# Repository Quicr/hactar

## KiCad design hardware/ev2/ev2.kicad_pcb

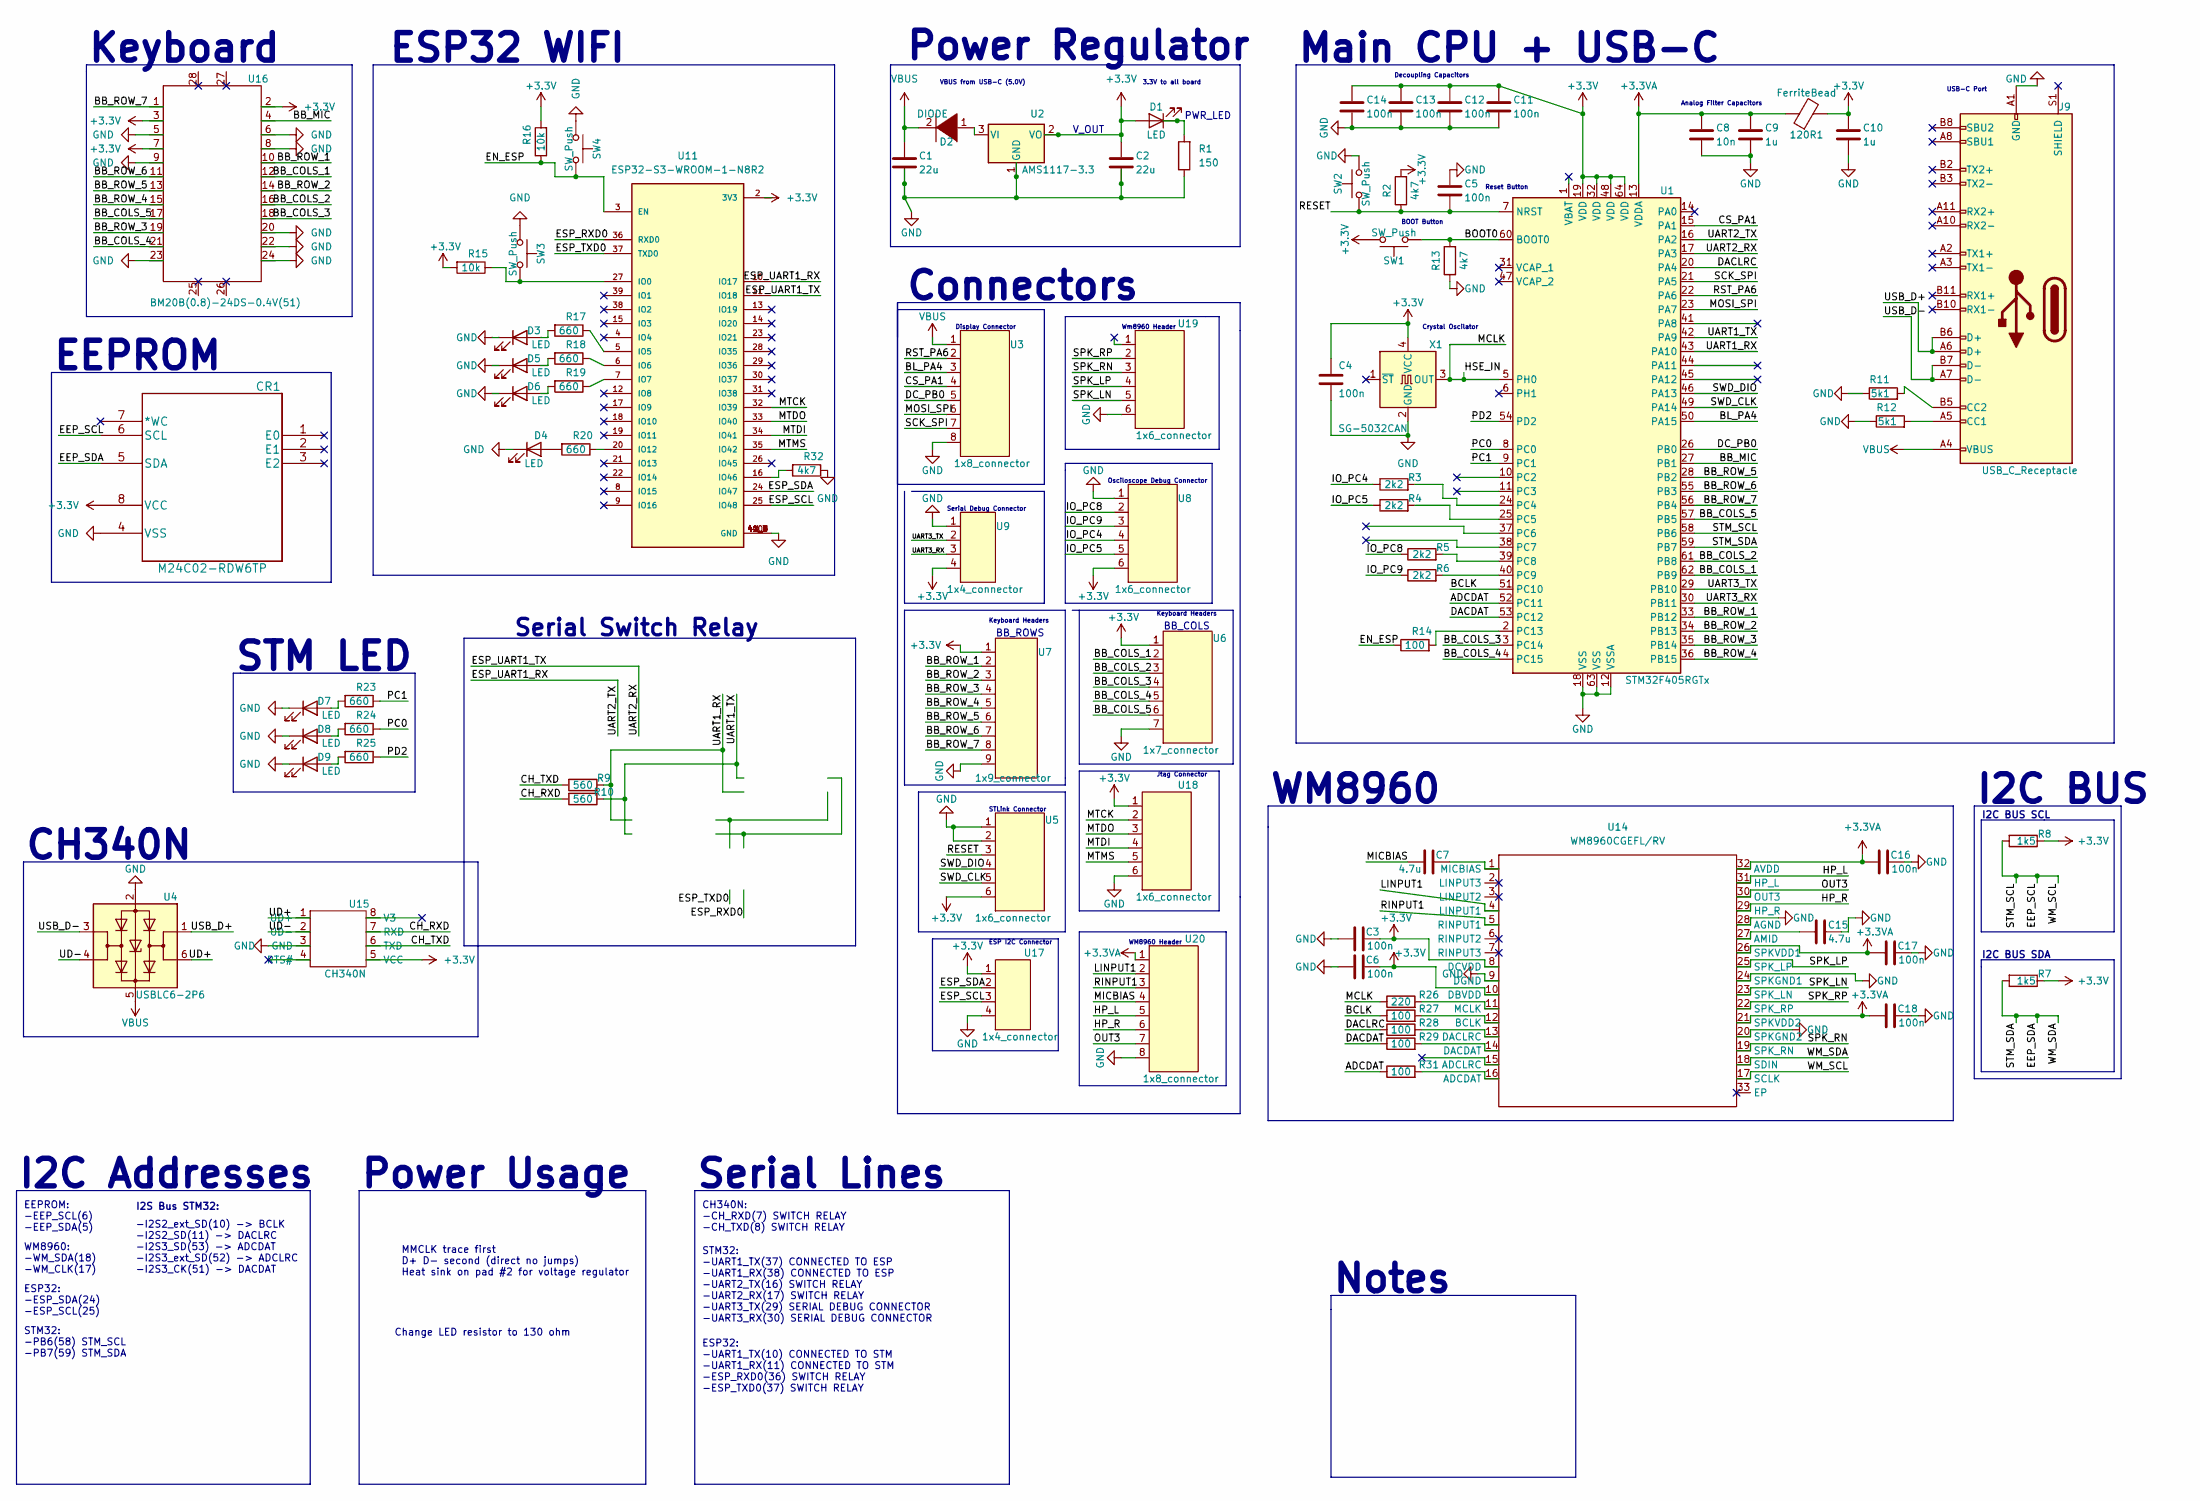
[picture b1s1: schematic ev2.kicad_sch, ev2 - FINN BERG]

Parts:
120R1: FerriteBead; L_0805_2012Metric
C1, C2: 22u; C_0805_2012Metric
C3, C4, C5, C6, C11, C12, C13, C14, C16, C17, C18: 100n; C_0805_2012Metric
C7, C15: 4.7u; C_0805_2012Metric
C8: 10n; C_0805_2012Metric
C9, C10: 1u; C_0805_2012Metric
CR1: M24C02-RDW6TP; New_ESP32_M24C02-RMN6TP
D1, D3, D4, D5, D6, D7, D8, D9: LED; LED_0805_2012Metric
D2: DIODE; D_0805_2012Metric
J9: USB_C_Receptacle; USB_C_Receptacle_HRO_TYPE-C-31-M-12
R1: 150; R_0805_2012Metric
R2, R13, R32: 4k7; R_0805_2012Metric
R3, R4, R5, R6: 2k2; R_0805_2012Metric
R7, R8: 1k5; R_0805_2012Metric
R9, R10: 560; R_0805_2012Metric
R11, R12: 5k1; R_0805_2012Metric
R14, R27, R28, R29, R31: 100; R_0805_2012Metric
R15, R16: 10k; R_0805_2012Metric
R17, R18, R19, R20, R23, R24, R25: 660; R_0805_2012Metric
R26: 220; R_0805_2012Metric
SW1, SW2, SW3, SW4: SW_Push; SW_DIP_SPSTx01_Slide_6.7x4.1mm_W6.73mm_P2.54mm_LowProfile_J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
U1: STM32F405RGTx; LQFP-64_10x10mm_P0.5mm
U2: AMS1117-3.3; SOT-223-3_TabPin2
U3, U20: 1x8_connector; 1X8_CONNECTOR
U4: USBLC6-2P6; SOT-666
U5, U8, U18, U19: 1x6_connector
U6: 1x7_connector
U7: 1x9_connector
U9, U17: 1x4_connector
U11: ESP32-S3-WROOM-1-N8R2
U14: WM8960CGEFL/RV; QFN50P500X500X90-33N
U15: CH340N; SOIC127P600X180-16N
U16: BM20B(0.8)-24DS-0.4V(51)
X1: SG-5032CAN; Oscillator_SMD_SeikoEpson_SG8002LB-4Pin_5.0x3.2mm

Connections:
+3.3V: 120R1.2, C2.1, C3.2, C4.1, C6.2, C10.1, C11.1, C12.1, C13.1, C14.1, CR1.8 (VCC), D1.2 (A), R2.2, R7.1, R8.1, R15.2, R16.2, SW1.1, U1.19 (VDD), U1.32 (VDD), U1.48 (VDD), U1.64 (VDD), U2.2 (VO), U5.6, U6.1, U7.1, U8.6, U9.4, U11.2 (3V3), U14.8 (DCVDD), U14.10 (DBVDD), U15.5 (VCC), U16.2, U16.3, U16.7, U17.1, U18.1, X1.4 (VCC)
+3.3VA: 120R1.1, C8.1, C9.1, C16.1, C17.1, C18.1, U1.13 (VDDA), U14.21 (SPKVDD2), U14.26 (SPKVDD1), U14.32 (AVDD), U20.1
/ADCDAT: R31.1, U1.52 (PC11)
/BB_COLS_1: U1.62 (PB9), U6.2, U16.12
/BB_COLS_2: U1.61 (PB8), U6.3, U16.16
/BB_COLS_3: U1.3 (PC14), U6.4, U16.18
/BB_COLS_4: U1.4 (PC15), U6.5, U16.21
/BB_COLS_5: U1.57 (PB5), U6.6, U16.17
/BB_MIC: U1.27 (PB1), U16.4
/BB_ROW_1: U1.33 (PB12), U7.2, U16.10
/BB_ROW_2: U1.34 (PB13), U7.3, U16.14
/BB_ROW_3: U1.35 (PB14), U7.4, U16.19
/BB_ROW_4: U1.36 (PB15), U7.5, U16.15
/BB_ROW_5: U1.28 (PB2), U7.6, U16.13
/BB_ROW_6: U1.55 (PB3), U7.7, U16.11
/BB_ROW_7: U1.56 (PB4), U7.8, U16.1
/BCLK: R27.1, U1.51 (PC10)
/BL_PA4: U1.50 (PA15), U3.3
/BOOT0: R13.2, SW1.2, U1.60 (BOOT0)
/CH_RXD: R10.2, U15.7 (RXD)
/CH_TXD: R9.2, U15.6 (TXD)
/CS_PA1: U1.15 (PA1), U3.4
/DACDAT: R29.1, U1.53 (PC12)
/DACLRC: R28.1, U1.20 (PA4)
/DC_PB0: U1.26 (PB0), U3.5
/EEP_SCL: CR1.6 (SCL), R8.2, U1.58 (PB6), U14.17 (SCLK)
/EEP_SDA: CR1.5 (SDA), R7.2, U1.59 (PB7), U14.18 (SDIN)
/EN_ESP: R14.1, R16.1, SW4.1, U11.3 (EN)
/ESP_RXD0: U11.36 (RXD0)
/ESP_SCL: U11.25 (IO48), U17.3
/ESP_SDA: U11.24 (IO47), U17.2
/ESP_TXD0: U11.37 (TXD0)
/ESP_UART1_RX: U1.16 (PA2), U11.10 (IO17)
/ESP_UART1_TX: U1.17 (PA3), U11.11 (IO18)
/HP_L: U14.31 (HP_L), U20.5
/HP_R: U14.29 (HP_R), U20.6
/HSE_IN: R26.1, U1.5 (PH0), X1.3 (OUT)
/IO_PC4: R3.1, U8.4
/IO_PC5: R4.1, U8.5
/IO_PC8: R5.1, U8.2
/IO_PC9: R6.1, U8.3
/LINPUT1: U14.4 (LINPUT1), U20.2
/MICBIAS: C7.1, U20.4
/MOSI_SPI: U1.23 (PA7), U3.6
/MTCK: U11.32 (IO39), U18.2
/MTDI: U11.34 (IO41), U18.4
/MTDO: U11.33 (IO40), U18.3
/MTMS: U11.35 (IO42), U18.5
/OUT3: U14.30 (OUT3), U20.7
/PC0: R24.1, U1.8 (PC0)
/PC1: R23.1, U1.9 (PC1)
/PD2: R25.1, U1.54 (PD2)
/RESET: C5.2, R2.1, SW2.2, U1.7 (NRST), U5.3
/RINPUT1: U14.5 (RINPUT1), U20.3
/RST_PA6: U1.22 (PA6), U3.2
/SCK_SPI: U1.21 (PA5), U3.7
/SPK_LN: U14.23 (SPK_LN), U19.5
/SPK_LP: U14.25 (SPK_LP), U19.4
/SPK_RN: U14.19 (SPK_RN), U19.3
/SPK_RP: U14.22 (SPK_RP), U19.2
/SWD_CLK: U1.49 (PA14), U5.5
/SWD_DIO: U1.46 (PA13), U5.4
/UART1_RX: R9.1, U1.43 (PA10)
/UART1_TX: R10.1, U1.42 (PA9)
/UART3_RX: U1.30 (PB11), U9.3
/UART3_TX: U1.29 (PB10), U9.2
/UD+: U4.6 (I/O1), U15.1 (UD+)
/UD-: U4.4 (I/O2), U15.2 (UD-)
/USB_D+: J9.A6 (D+), J9.B6 (D+), U4.1 (I/O1)
/USB_D-: J9.A7 (D-), J9.B7 (D-), U4.3 (I/O2)
GND: C1.2, C2.2, C3.1, C4.2, C5.1, C6.1, C8.2, C9.2, C10.2, C11.2, C12.2, C13.2, C14.2, C15.1, C16.2, C17.2, C18.2, CR1.4 (VSS), D3.1 (K), D4.1 (K), D5.1 (K), D6.1 (K), D7.1 (K), D8.1 (K), D9.1 (K), J9.A1 (GND), J9.A12 (GND), J9.B1 (GND), J9.B12 (GND), R1.1, R11.1, R12.1, R13.1, R32.1, SW2.1, SW3.2, SW4.2, U1.12 (VSSA), U1.18 (VSS), U1.63 (VSS), U2.1 (GND), U3.8, U4.2 (GND), U5.1, U5.2, U6.7, U7.9, U8.1, U9.1, U11.1 (GND), U11.40 (GND), U11.41_1 (GND), U11.41_2 (GND), U11.41_3 (GND), U11.41_4 (GND), U11.41_5 (GND), U11.41_6 (GND), U11.41_7 (GND), U11.41_8 (GND), U11.41_9 (GND), U14.9 (DGND), U14.20 (SPKGND2), U14.24 (SPKGND1), U14.28 (AGND), U15.3 (GND), U16.5, U16.6, U16.8, U16.9, U16.20, U16.22, U16.23, U16.24, U17.4, U18.6, U19.6, U20.8, X1.2 (GND)
unnamed: C7.2, U14.1 (MICBIAS)
unnamed: C15.2, U14.27 (AMID)
unnamed: D1.1 (K), R1.2
unnamed: D2.1 (K), U2.3 (VI)
unnamed: D3.2 (A), R17.2
unnamed: D4.2 (A), R20.2
unnamed: D5.2 (A), R18.2
unnamed: D6.2 (A), R19.2
unnamed: D7.2 (A), R23.2
unnamed: D8.2 (A), R24.2
unnamed: D9.2 (A), R25.2
unnamed: J9.A5 (CC1), R12.2
unnamed: J9.B5 (CC2), R11.2
unnamed: R3.2, U1.24 (PC4)
unnamed: R4.2, U1.25 (PC5)
unnamed: R5.2, U1.39 (PC8)
unnamed: R6.2, U1.40 (PC9)
unnamed: R14.2, U1.2 (PC13)
unnamed: R15.1, SW3.1, U11.27 (IO0)
unnamed: R17.1, U11.5 (IO5)
unnamed: R18.1, U11.6 (IO6)
unnamed: R19.1, U11.7 (IO7)
unnamed: R20.1, U11.20 (IO12)
unnamed: R26.2, U14.11 (MCLK)
unnamed: R27.2, U14.12 (BCLK)
unnamed: R28.2, U14.13 (DACLRC)
unnamed: R29.2, U14.14 (DACDAT)
unnamed: R31.2, U14.16 (ADCDAT)
unnamed: R32.2, U11.16 (IO46)
VBUS: C1.1, D2.2 (A), J9.A4 (VBUS), J9.A9 (VBUS), J9.B4 (VBUS), J9.B9 (VBUS), U3.1, U4.5 (VBUS)

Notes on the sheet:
STM32: -UART1_TX(37) CONNECTED TO ESP -UART1_RX(38) CONNECTED TO ESP -UART2_TX(16) SWITCH RELAY -UART2_RX(17) SWITCH RELAY -UART3_TX(29) SERIAL DEBUG CONNECTOR -UART3_RX(30) SERIAL DEBUG CONNECTOR
Serial Switch Relay
EEPROM: -EEP_SCL(6) -EEP_SDA(5)
I2S Bus STM32:
BB_COLS
ESP32: -ESP_SDA(24) -ESP_SCL(25)
ESP32 WIFI
Analog Filter Capacitors
I2C BUS SCL
PWR_LED
Keyboard Headers
Crystal Oscilator
CH340N: -CH_RXD(7) SWITCH RELAY -CH_TXD(8) SWITCH RELAY
3.3V to all board
BB_ROWS
Decoupling Capacitors
Main CPU + USB-C
Serial Debug Connector
-I2S2_ext_SD(10) -> BCLK -I2S2_SD(11) -> DACLRC -I2S3_SD(53) -> ADCDAT -I2S3_ext_SD(52) -> ADCLRC -I2S3_CK(51) -> DACDAT
ESP32: -UART1_TX(10) CONNECTED TO STM -UART1_RX(11) CONNECTED TO STM -ESP_RXD0(36) SWITCH RELAY -ESP_TXD0(37) SWITCH RELAY
Notes
MMCLK trace first D+ D- second (direct no jumps) Heat sink on pad #2 for voltage regulator
Power Usage
WM8960
I2C BUS SDA
V_OUT
STM32: -PB6(58) STM_SCL -PB7(59) STM_SDA
EEPROM
Display Connector
I2C BUS
WM8960: -WM_SDA(18) -WM_CLK(17)
I2C Addresses
VBUS from USB-C (5.0V)
Serial Lines
Power Regulator
Keyboard
Change LED resistor to 130 ohm
Connectors
WM8960 Header
STLink Connector

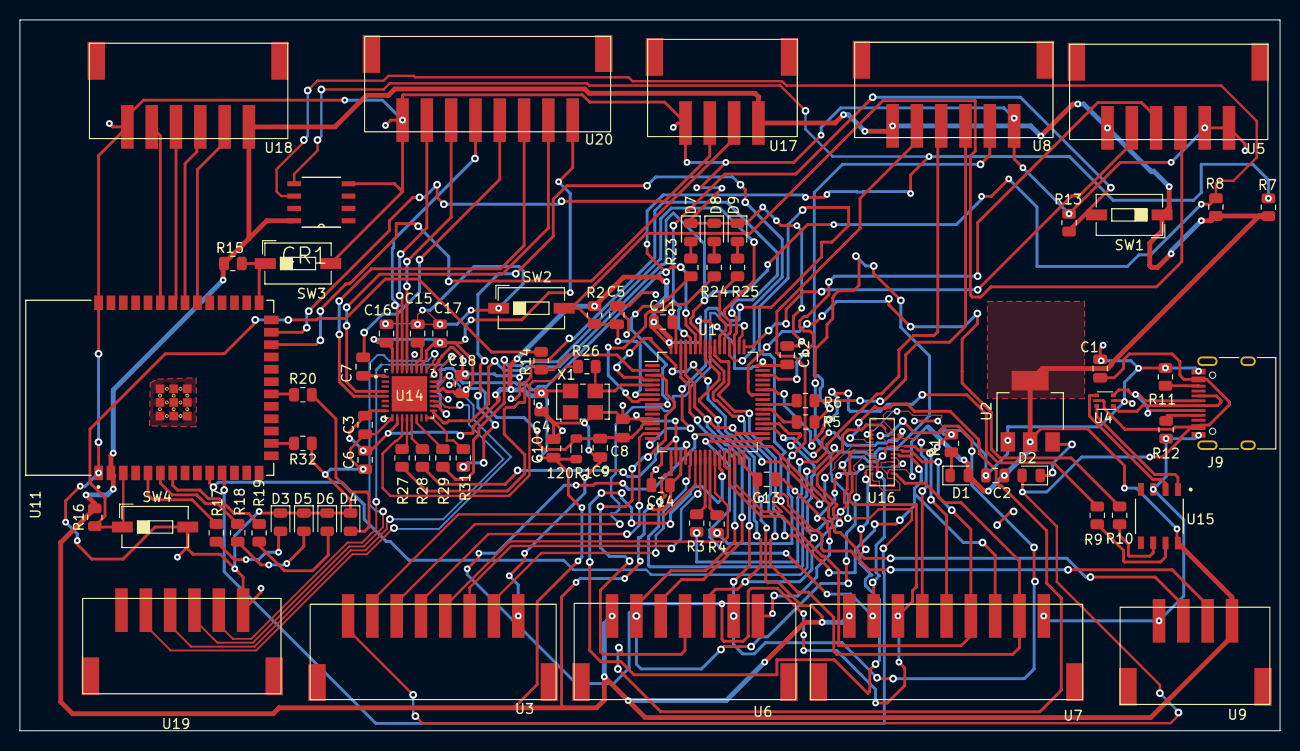
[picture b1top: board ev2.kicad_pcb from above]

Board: 2 copper layers, 129.6 x 73.1 mm, 81 parts (0 on the bottom side), 99 nets.

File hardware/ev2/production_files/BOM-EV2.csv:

Comment,Designator,Footprint,LCSC
FerriteBead,120R1,L_0805_2012Metric,C127301
LED,"D1,D3,D4,D5,D6,D7,D8,D9",LED_0805_2012Metric,C130114
DIODE,D2,D_0805_2012Metric,C133103
STM32F405RGTx,U1,LQFP-64_10x10mm_P0.5mm,C15742
USB_C_Receptacle,J9,USB_C_Receptacle_HRO_TYPE-C-31-M-12,C165948
10n,C8,C_0805_2012Metric,C1710
660,"R17,R18,R19,R20,R23,R24,R25",R_0805_2012Metric,C17455
150,R1,R_0805_2012Metric,C17471
2k2,"R3,R4,R5,R6",R_0805_2012Metric,C17520
4k7,"R13,R2,R32",R_0805_2012Metric,C17673
WM8960CGEFL/RV,U14,QFN50P500X500X90-33N,C18752
SG-5032CAN,X1,Oscillator_SMD_SeikoEpson_SG8002LB-4Pin_5.0x3.2mm,C1987261
100,"R14,R27,R28,R29,R31",R_0805_2012Metric,C212282
SW_Push,"SW1,SW2,SW3,SW4",SW_DIP_SPSTx01_Slide_6.7x4.1mm_W6.73mm_P2.54mm_LowProfile_JPin,C266189
5k1,"R11,R12",R_0805_2012Metric,C27834
USBLC6-2P6,U4,SOT-666,C2827693
1u,"C10,C9",C_0805_2012Metric,C28323
1x4_connector,"U17,U9",1x4_connector,C2845685
1x6_connector,"U18,U19,U5,U8",1x6_connector,C2845687
1x7_connector,U6,1x7_connector,C2845688
1x8_connector,"U20,U3",1X8_CONNECTOR,C2845689
1x9_connector,U7,1x9_connector,C2845690
ESP32-S3-WROOM-1-N8R2,U11,ESP32-S3-WROOM-1-N8R2,C2913204
SW_DIP_x02,"SW5,SW6,SW7,SW8",SW_DIP_SPSTx02_Slide_6.7x6.64mm_W6.73mm_P2.54mm_LowProfile_JPin,C3293152
AMS1117-3.3,U2,SOT-223-3_TabPin2,C351784
560,"R10,R21,R22,R9",R_0805_2012Metric,C374648
220,R26,R_0805_2012Metric,C374734
4.7u,"C15,C7",C_0805_2012Metric,C412634
BM20B(0.8)-24DS-0.4V(51),U16,BM20B(0.8)-24DS-0.4V(51),C424537
1k5,"R7,R8",R_0805_2012Metric,C4310
22u,"C1,C2",C_0805_2012Metric,C45783
10k,"R15,R16",R_0805_2012Metric,C465472
100n,"C11,C12,C13,C14,C16,C17,C18,C3,C4,C5,C6",C_0805_2012Metric,C49678
CH340N,U15,SOIC127P600X180-16N,C506813
M24C02-RDW6TP,CR1,M24C02-RDW6TP,C83836

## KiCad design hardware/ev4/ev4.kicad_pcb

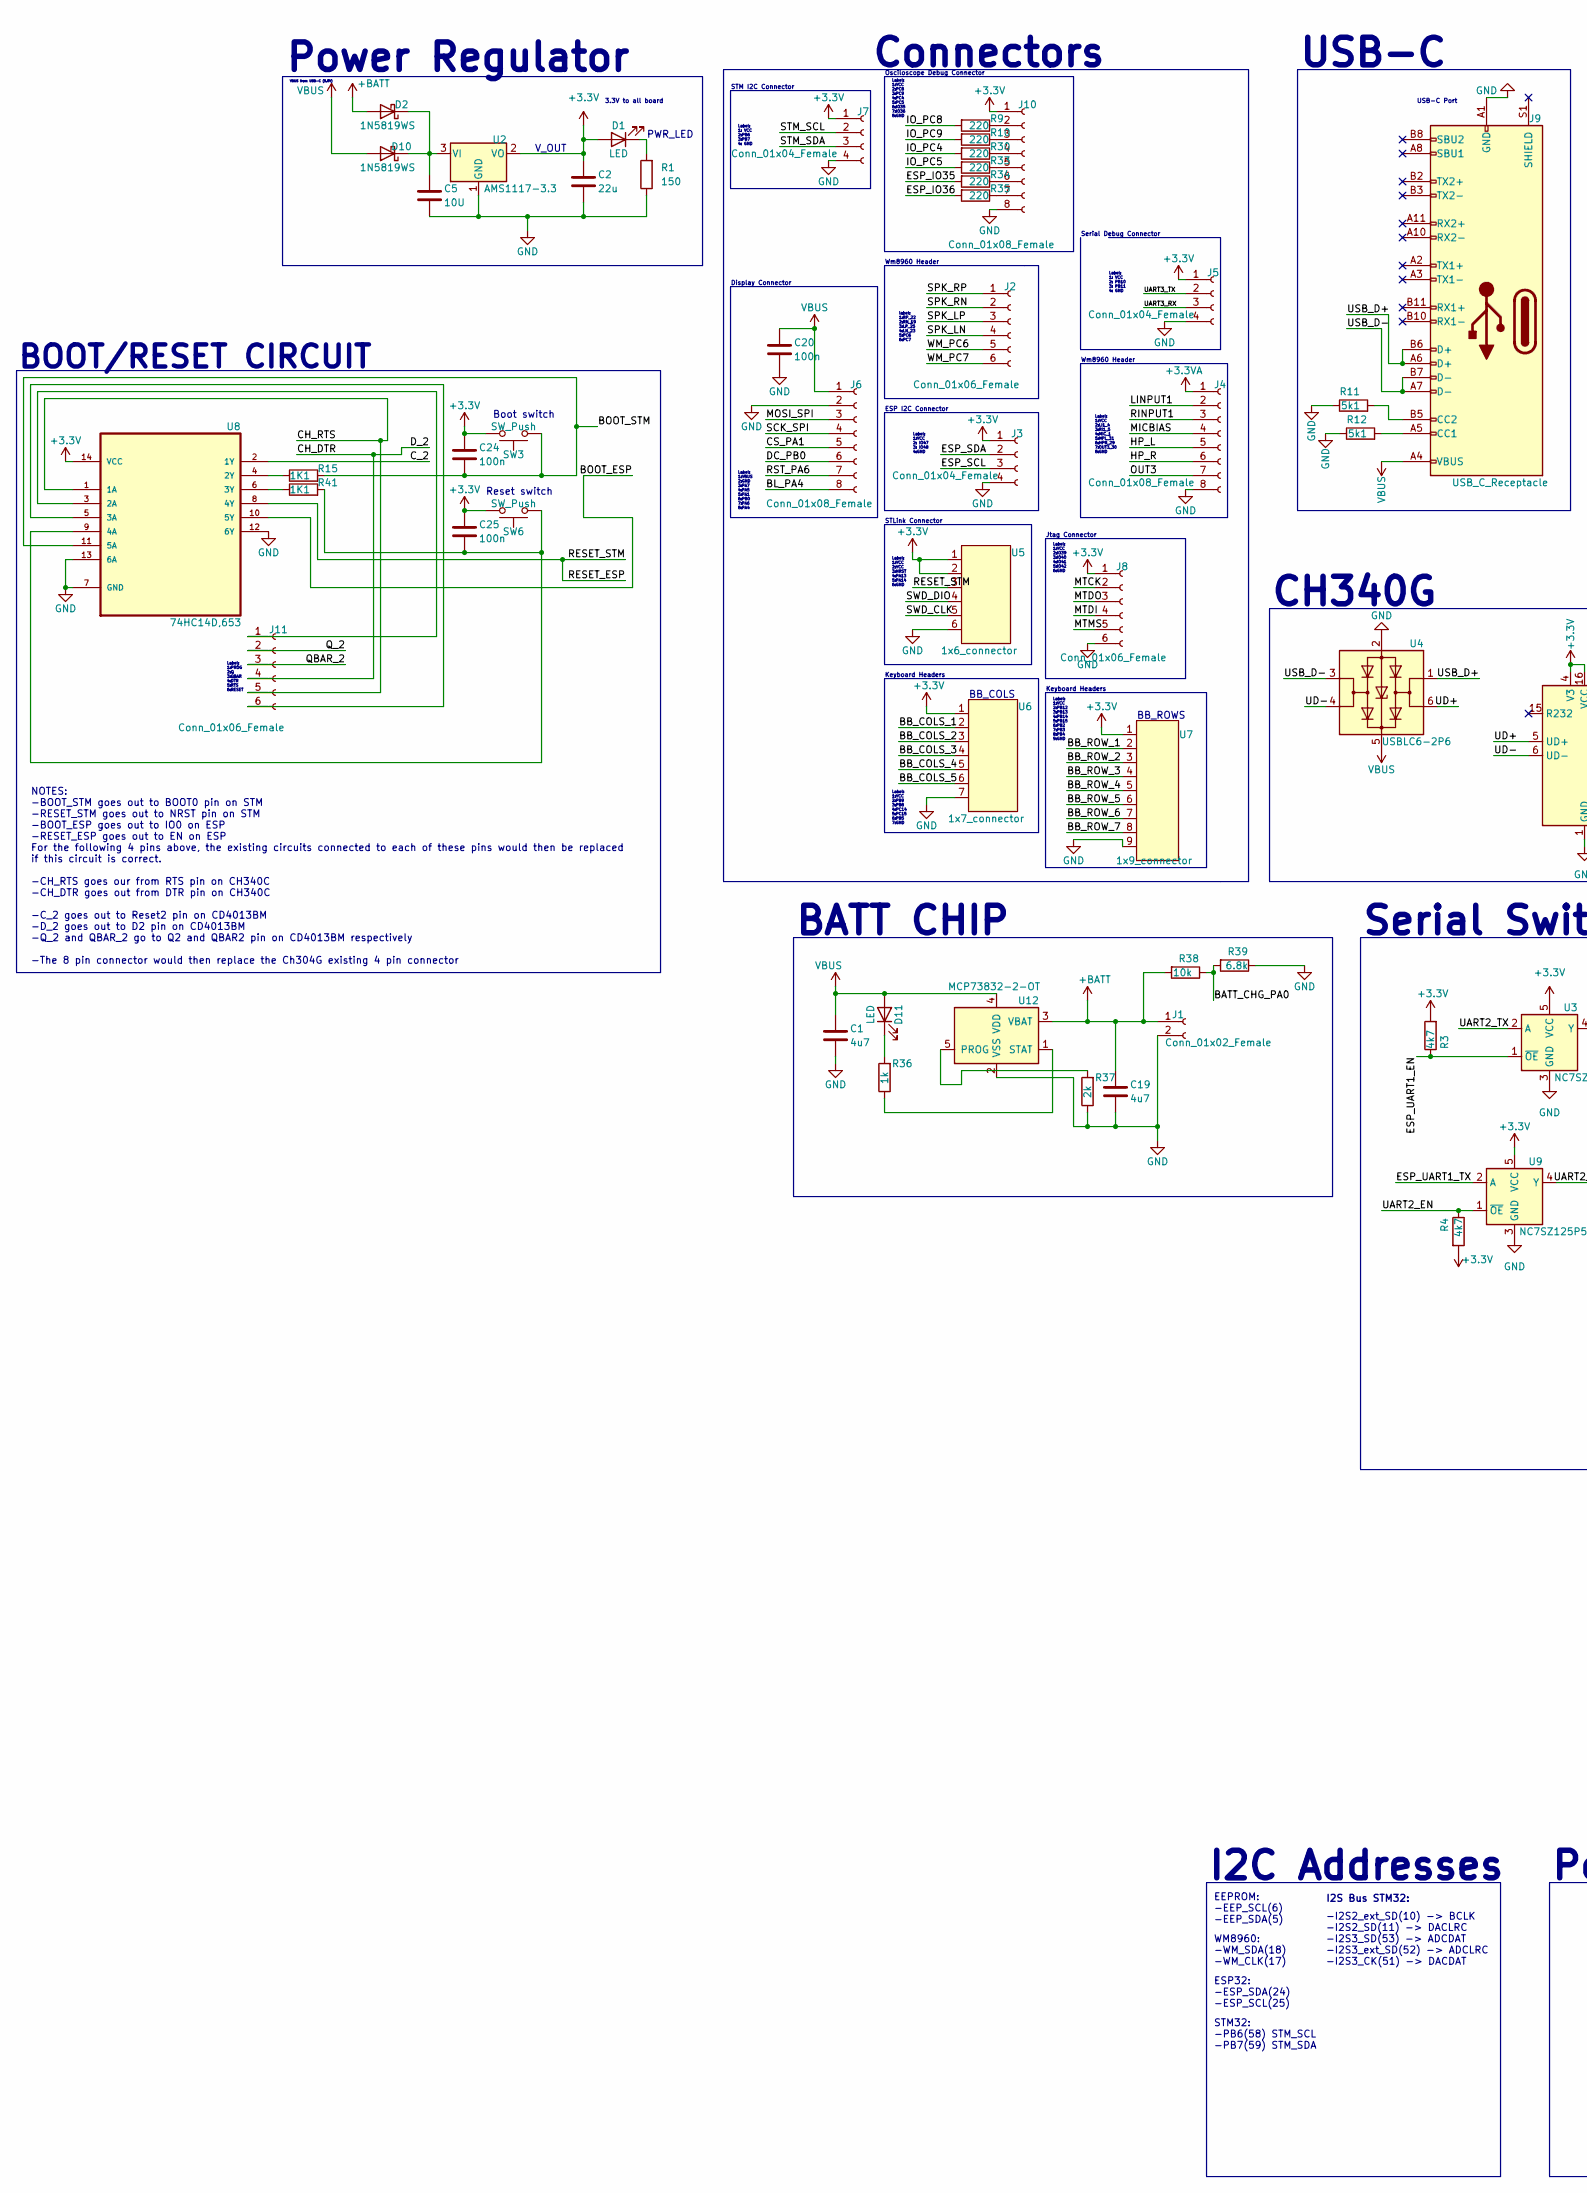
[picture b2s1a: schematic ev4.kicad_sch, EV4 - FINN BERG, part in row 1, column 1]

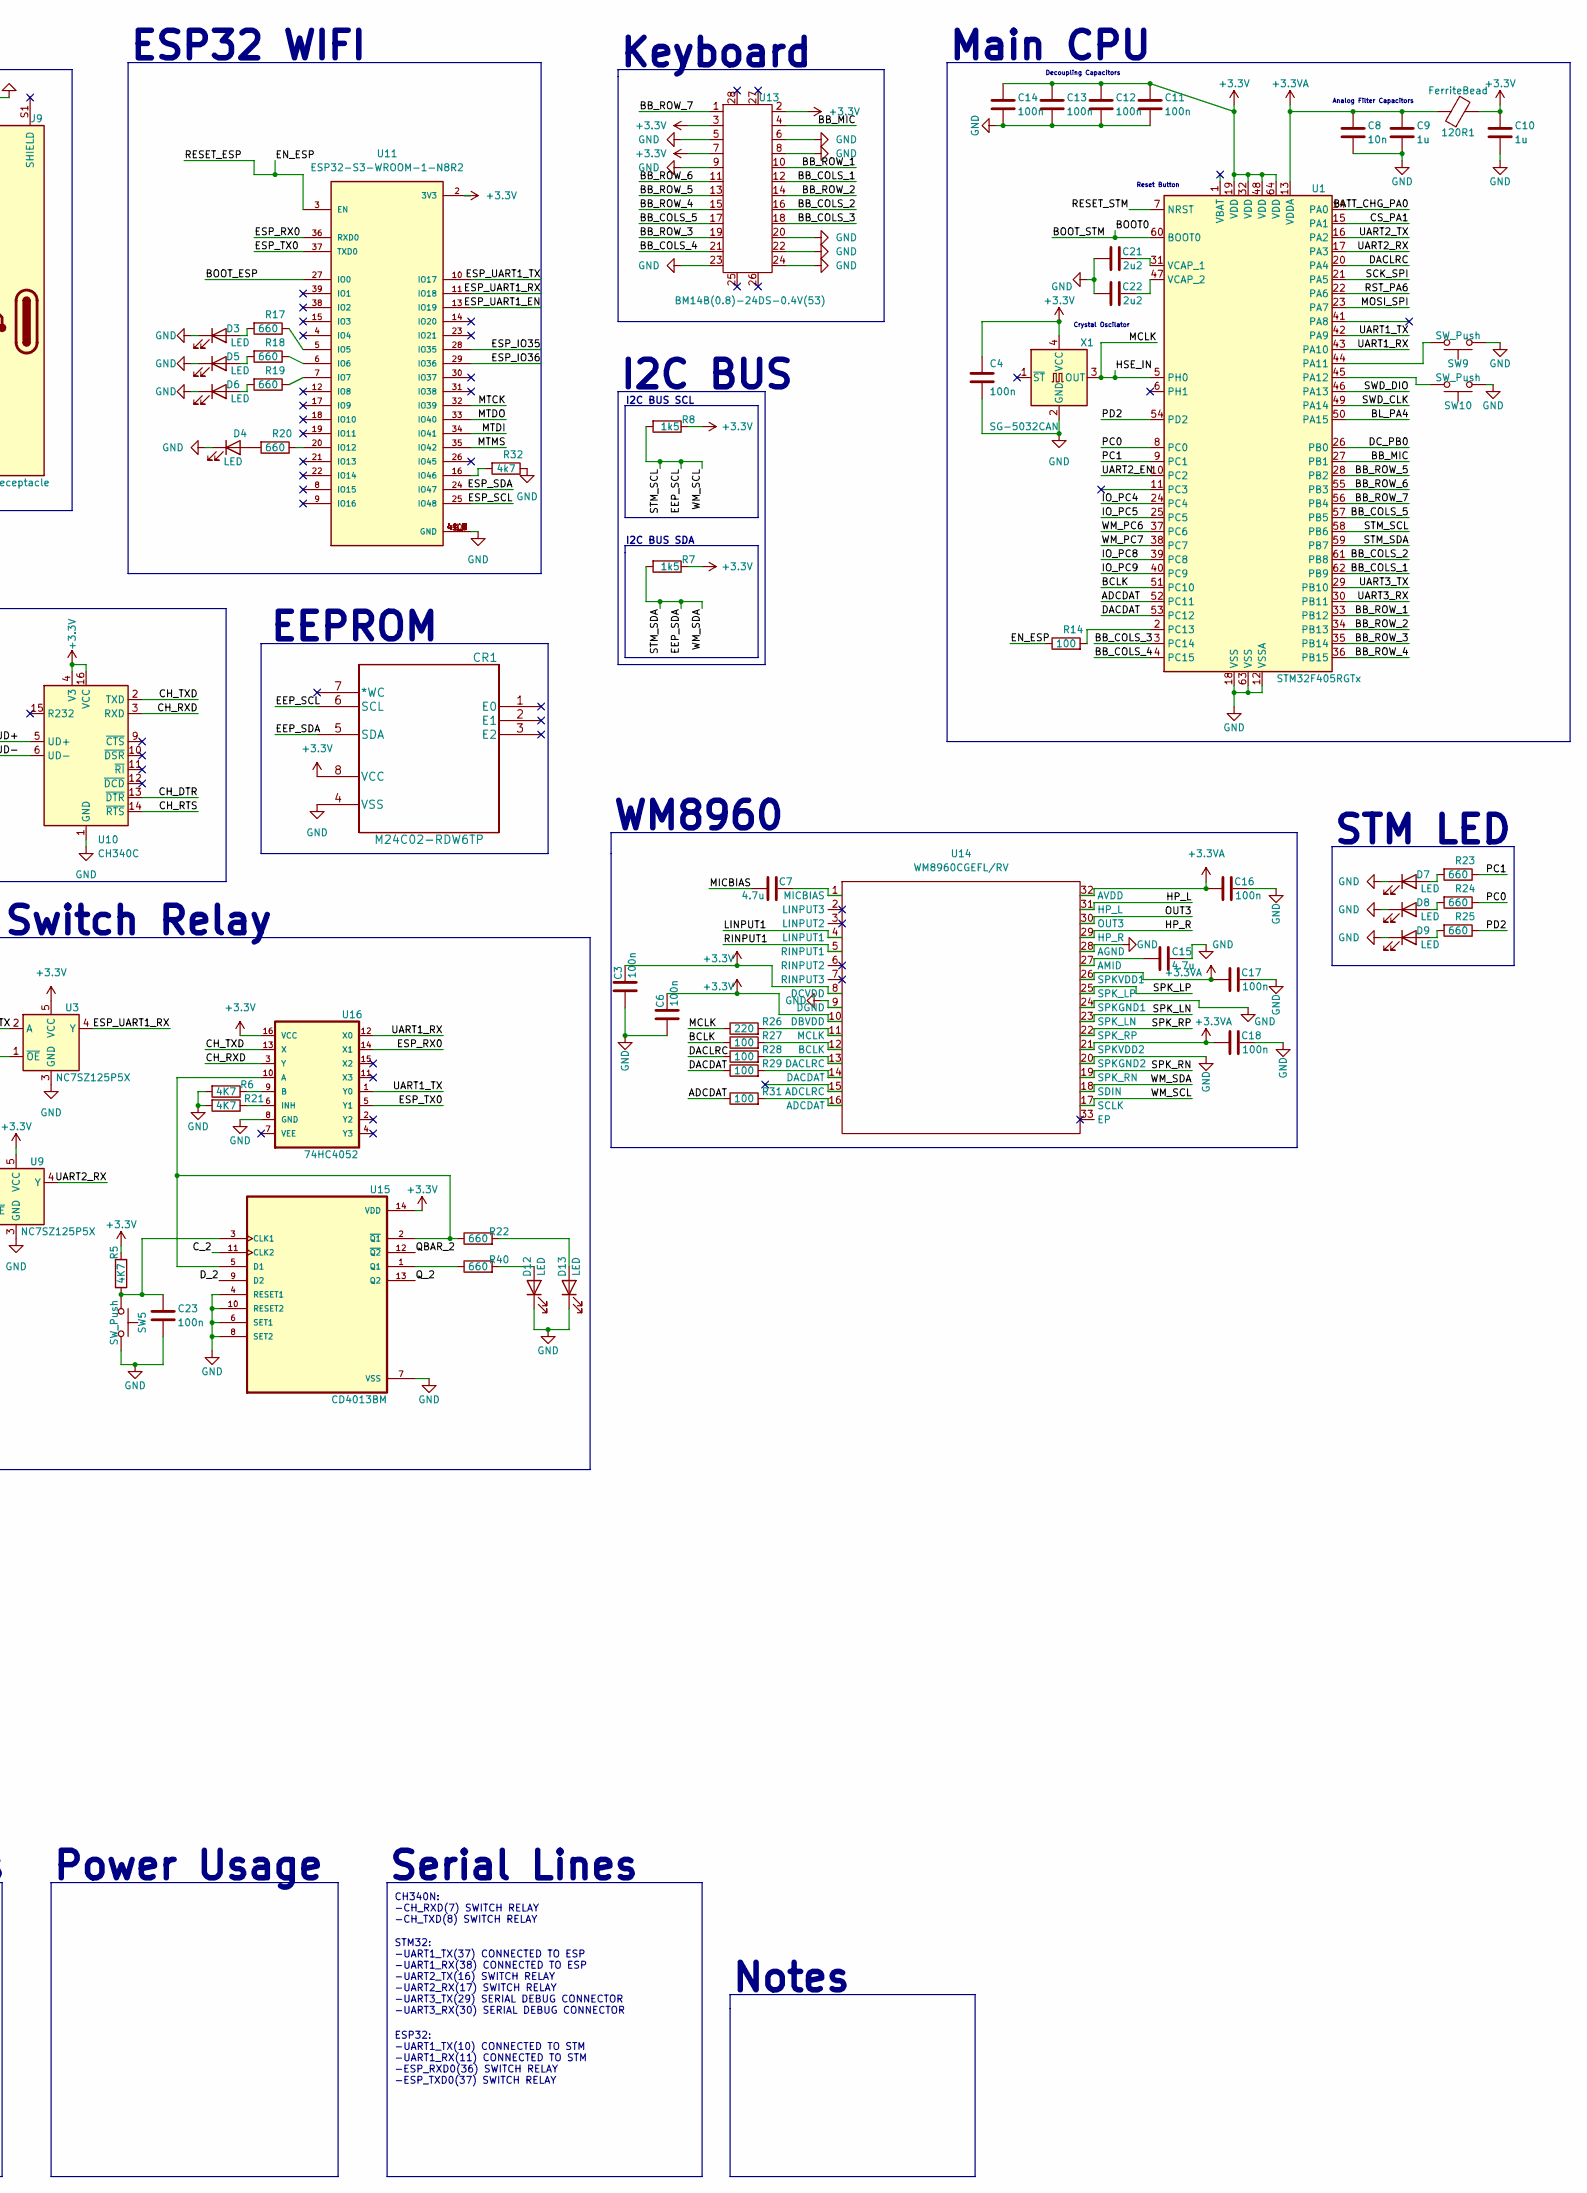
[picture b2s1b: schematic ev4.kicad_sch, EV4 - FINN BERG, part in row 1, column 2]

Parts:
120R1: FerriteBead; L_0603_1608Metric
C1, C19: 4u7; C_0805_2012Metric
C2: 22u; C_0805_2012Metric
C3, C4, C6, C11, C12, C13, C14, C16, C17, C18, C20, C23, C24, C25: 100n; C_0805_2012Metric
C5: 10U; C_0805_2012Metric
C7, C15: 4.7u; C_0805_2012Metric
C8: 10n; C_0805_2012Metric
C9, C10: 1u; C_0805_2012Metric
C21, C22: 2u2; C_0603_1608Metric
CR1: M24C02-RDW6TP; New_ESP32_M24C02-RMN6TP
D1, D3, D4, D5, D6, D7, D8, D9, D11, D12, D13: LED; LED_0805_2012Metric
D2, D10: 1N5819WS; D_SOD-323
J1: Conn_01x02_Female; JST_PH_S2B-PH-SM4-TB_1x02-1MP_P2.00mm_Horizontal
J2, J8, J11: Conn_01x06_Female; JST_PH_S6B-PH-SM4-TB_1x06-1MP_P2.00mm_Horizontal
J3, J5, J7: Conn_01x04_Female; JST_PH_S4B-PH-SM4-TB_1x04-1MP_P2.00mm_Horizontal
J4, J6, J10: Conn_01x08_Female; JST_PH_S8B-PH-SM4-TB_1x08-1MP_P2.00mm_Horizontal
J9: USB_C_Receptacle; USB_C_Receptacle_HRO_TYPE-C-31-M-12
R1: 150; R_0805_2012Metric
R3, R4, R32: 4k7; R_0805_2012Metric
R5, R6, R21: 4K7; R_0805_2012Metric
R7, R8: 1k5; R_0805_2012Metric
R9, R10, R26, R30, R33, R34, R35: 220; R_0805_2012Metric
R11, R12: 5k1; R_0805_2012Metric
R14, R27, R28, R29, R31: 100; R_0805_2012Metric
R15, R41: 1K1; R_0805_2012Metric
R17, R18, R19, R20, R22, R23, R24, R25, R40: 660; R_0805_2012Metric
R36: 1k; R_0805_2012Metric
R37: 2k; R_0805_2012Metric
R38: 10k; R_0805_2012Metric
R39: 6.8k; R_0805_2012Metric
SW3, SW5, SW6, SW9, SW10: SW_Push; SW_DIP_SPSTx01_Slide_6.7x4.1mm_W6.73mm_P2.54mm_LowProfile_J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
U1: STM32F405RGTx; LQFP-64_10x10mm_P0.5mm
U2: AMS1117-3.3; SOT-223-3_TabPin2
U3, U9: NC7SZ125P5X; SOT-353_SC-70-5
U4: USBLC6-2P6; SOT-666
U5: 1x6_connector
U6: 1x7_connector
U7: 1x9_connector
U8: 74HC14D,653; SOIC127P600X175-14N; MPN 74HCT14D,653
U10: CH340C; SOIC-16_3.9x9.9mm_P1.27mm
U11: ESP32-S3-WROOM-1-N8R2; ESP32-S3-WROOM-1U
U12: MCP73832-2-OT; SOT-23-5
U13: BM14B(0.8)-24DS-0.4V(53); BM14B(0.B)-24DS-0.4V(53)
U14: WM8960CGEFL/RV; QFN50P500X500X90-33N
U15: CD4013BM; SOIC127P600X175-14N
U16: 74HC4052; SO16
X1: SG-5032CAN; Oscillator_SMD_SeikoEpson_SG8002LB-4Pin_5.0x3.2mm

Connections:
+3.3V: 120R1.2, C2.1, C3.2, C4.1, C6.2, C10.1, C11.1, C12.1, C13.1, C14.1, C24.1, C25.1, CR1.8 (VCC), D1.2 (A), J3.1, J5.1, J7.1, J8.1, J10.1, R3.2, R4.2, R5.1, R7.1, R8.1, SW3.1, SW6.1, U1.19 (VDD), U1.32 (VDD), U1.48 (VDD), U1.64 (VDD), U2.2 (VO), U3.5 (VCC), U5.1, U5.2, U6.1, U7.1, U8.14 (VCC), U9.5 (VCC), U10.4 (V3), U10.16 (VCC), U11.2 (3V3), U13.2, U13.3, U13.7, U14.8 (DCVDD), U14.10 (DBVDD), U15.14 (VDD), U16.16 (VCC), X1.4 (VCC)
+3.3VA: 120R1.1, C8.1, C9.1, C16.1, C17.1, C18.1, J4.1, U1.13 (VDDA), U14.21 (SPKVDD2), U14.26 (SPKVDD1), U14.32 (AVDD)
+BATT: C19.1, D2.2 (A), J1.1, R38.2, U12.3 (VBAT)
/ADCDAT: R31.1, U1.52 (PC11)
/BATT_CHG_PA0: R38.1, R39.2, U1.14 (PA0)
/BB_COLS_1: U1.62 (PB9), U6.2, U13.12
/BB_COLS_2: U1.61 (PB8), U6.3, U13.16
/BB_COLS_3: U1.3 (PC14), U6.4, U13.18
/BB_COLS_4: U1.4 (PC15), U6.5, U13.21
/BB_COLS_5: U1.57 (PB5), U6.6, U13.17
/BB_MIC: U1.27 (PB1), U13.4
/BB_ROW_1: U1.33 (PB12), U7.2, U13.10
/BB_ROW_2: U1.34 (PB13), U7.3, U13.14
/BB_ROW_3: U1.35 (PB14), U7.4, U13.19
/BB_ROW_4: U1.36 (PB15), U7.5, U13.15
/BB_ROW_5: U1.28 (PB2), U7.6, U13.13
/BB_ROW_6: U1.55 (PB3), U7.7, U13.11
/BB_ROW_7: U1.56 (PB4), U7.8, U13.1
/BCLK: R27.1, U1.51 (PC10)
/BL_PA4: J6.8, U1.50 (PA15)
/BOOT0: C24.2, R15.2, SW3.2, U1.60 (BOOT0), U8.11 (5A)
/BOOT_ESP: U8.10 (5Y), U11.27 (IO0)
/CH_DTR: J11.4, U10.13 (~DTR), U15.9 (D2)
/CH_RTS: J11.5, U8.1 (1A), U10.14 (~RTS)
/CH_RXD: U10.3 (RXD), U16.3 (Y)
/CH_TXD: U10.2 (TXD), U16.13 (X)
/CS_PA1: J6.5, U1.15 (PA1)
/C_2: U8.2 (1Y), U15.11 (CLK2)
/DACDAT: R29.1, U1.53 (PC12)
/DACLRC: R28.1, U1.20 (PA4)
/DC_PB0: J6.6, U1.26 (PB0)
/EEP_SCL: CR1.6 (SCL), J7.2, R8.2, U1.58 (PB6), U14.17 (SCLK)
/EEP_SDA: CR1.5 (SDA), J7.3, R7.2, U1.59 (PB7), U14.18 (SDIN)
/EN_ESP: R14.1, U1.7 (NRST), U5.3, U8.8 (4Y), U11.3 (EN)
/ESP_IO35: R34.2, U11.28 (IO35)
/ESP_IO36: R35.2, U11.29 (IO36)
/ESP_RX0: U11.36 (RXD0), U16.14 (X1)
/ESP_SCL: J3.3, U11.25 (IO48)
/ESP_SDA: J3.2, U11.24 (IO47)
/ESP_TX0: U11.37 (TXD0), U16.5 (Y1)
/ESP_UART1_EN: R3.1, U3.1 (~OE), U11.13 (IO19)
/ESP_UART1_RX: U3.4 (Y), U11.11 (IO18)
/ESP_UART1_TX: U9.2 (A), U11.10 (IO17)
/HP_L: J4.5, U14.31 (HP_L)
/HP_R: J4.6, U14.29 (HP_R)
/HSE_IN: R26.1, U1.5 (PH0), X1.3 (OUT)
/IO_PC4: R30.2, U1.24 (PC4)
/IO_PC5: R33.2, U1.25 (PC5)
/IO_PC8: R9.2, U1.39 (PC8)
/IO_PC9: R10.2, U1.40 (PC9)
/LINPUT1: J4.2, U14.4 (LINPUT1)
/MICBIAS: C7.1, J4.4
/MOSI_SPI: J6.3, U1.23 (PA7)
/MTCK: J8.2, U11.32 (IO39)
/MTDI: J8.4, U11.34 (IO41)
/MTDO: J8.3, U11.33 (IO40)
/MTMS: J8.5, U11.35 (IO42)
/OUT3: J4.7, U14.30 (OUT3)
/PC0: R24.1, U1.8 (PC0)
/PC1: R23.1, U1.9 (PC1)
/PD2: R25.1, U1.54 (PD2)
/QBAR_2: J11.3, U15.12 (~Q2)
/Q_2: J11.2, U15.13 (Q2)
/RINPUT1: J4.3, U14.5 (RINPUT1)
/RST_PA6: J6.7, U1.22 (PA6)
/SCK_SPI: J6.4, U1.21 (PA5)
/SPK_LN: J2.4, U14.23 (SPK_LN)
/SPK_LP: J2.3, U14.25 (SPK_LP)
/SPK_RN: J2.2, U14.19 (SPK_RN)
/SPK_RP: J2.1, U14.22 (SPK_RP)
/SWD_CLK: U1.49 (PA14), U5.5
/SWD_DIO: U1.46 (PA13), U5.4
/UART1_RX: U1.43 (PA10), U16.12 (X0)
/UART1_TX: U1.42 (PA9), U16.1 (Y0)
/UART2_EN: R4.1, U1.10 (PC2), U9.1 (~OE)
/UART2_RX: U1.17 (PA3), U9.4 (Y)
/UART2_TX: U1.16 (PA2), U3.2 (A)
/UART3_RX: J5.3, U1.30 (PB11)
/UART3_TX: J5.2, U1.29 (PB10)
/UD+: U4.6 (I/O1), U10.5 (UD+)
/UD-: U4.4 (I/O2), U10.6 (UD-)
/USB_D+: J9.A6 (D+), J9.B6 (D+), U4.1 (I/O1)
/USB_D-: J9.A7 (D-), J9.B7 (D-), U4.3 (I/O2)
/WM_PC6: J2.5, U1.37 (PC6)
/WM_PC7: J2.6, U1.38 (PC7)
GND: C1.2, C2.2, C3.1, C4.2, C5.2, C6.1, C8.2, C9.2, C10.2, C11.2, C12.2, C13.2, C14.2, C15.1, C16.2, C17.2, C18.2, C19.2, C20.2, C21.1, C22.1, C23.2, CR1.4 (VSS), D3.1 (K), D4.1 (K), D5.1 (K), D6.1 (K), D7.1 (K), D8.1 (K), D9.1 (K), D12.1 (K), D13.1 (K), J1.2, J3.4, J4.8, J5.4, J6.2, J7.4, J8.6, J9.A1 (GND), J9.A12 (GND), J9.B1 (GND), J9.B12 (GND), J10.8, R1.1, R6.2, R11.1, R12.1, R21.2, R32.1, R37.1, R39.1, SW5.1, SW9.2, SW10.2, U1.12 (VSSA), U1.18 (VSS), U1.63 (VSS), U2.1 (GND), U3.3 (GND), U4.2 (GND), U5.6, U6.7, U7.9, U8.7 (GND), U8.12 (6Y), U8.13 (6A), U9.3 (GND), U10.1 (GND), U11.1 (GND), U11.40 (GND), U11.41_1 (GND), U11.41_2 (GND), U11.41_3 (GND), U11.41_4 (GND), U11.41_5 (GND), U11.41_6 (GND), U11.41_7 (GND), U11.41_8 (GND), U11.41_9 (GND), U12.2 (VSS), U13.5, U13.6, U13.8, U13.9, U13.20, U13.22, U13.23, U13.24, U14.9 (DGND), U14.20 (SPKGND2), U14.24 (SPKGND1), U14.28 (AGND), U15.4 (RESET1), U15.6 (SET1), U15.7 (VSS), U15.8 (SET2), U15.10 (RESET2), U16.8 (GND), X1.2 (GND)
unnamed: C7.2, U14.1 (MICBIAS)
unnamed: C15.2, U14.27 (AMID)
unnamed: C21.2, U1.31 (VCAP_1)
unnamed: C22.2, U1.47 (VCAP_2)
unnamed: C23.1, R5.2, SW5.2, U15.3 (CLK1)
unnamed: C25.2, R41.2, SW6.2, U8.9 (4A)
unnamed: D1.1 (K), R1.2
unnamed: D3.2 (A), R17.2
unnamed: D4.2 (A), R20.2
unnamed: D5.2 (A), R18.2
unnamed: D6.2 (A), R19.2
unnamed: D7.2 (A), R23.2
unnamed: D8.2 (A), R24.2
unnamed: D9.2 (A), R25.2
unnamed: C5.1, D2.1 (K), D10.1 (K), U2.3 (VI)
unnamed: D11.1 (K), R36.2
unnamed: D12.2 (A), R40.2
unnamed: D13.2 (A), R22.2
unnamed: J9.A5 (CC1), R12.2
unnamed: J9.B5 (CC2), R11.2
unnamed: J10.2, R9.1
unnamed: J10.3, R10.1
unnamed: J10.4, R30.1
unnamed: J10.5, R33.1
unnamed: J10.6, R34.1
unnamed: J10.7, R35.1
unnamed: R6.1, U16.9 (B)
unnamed: R14.2, U1.2 (PC13)
unnamed: R15.1, U8.4 (2Y)
unnamed: R17.1, U11.5 (IO5)
unnamed: R18.1, U11.6 (IO6)
unnamed: R19.1, U11.7 (IO7)
unnamed: R20.1, U11.20 (IO12)
unnamed: R21.1, U16.6 (INH)
unnamed: R22.1, U15.2 (~Q1), U15.5 (D1), U16.10 (A)
unnamed: R26.2, U14.11 (MCLK)
unnamed: R27.2, U14.12 (BCLK)
unnamed: R28.2, U14.13 (DACLRC)
unnamed: R29.2, U14.14 (DACDAT)
unnamed: R31.2, U14.16 (ADCDAT)
unnamed: R32.2, U11.16 (IO46)
unnamed: R36.1, U12.1 (STAT)
unnamed: R37.2, U12.5 (PROG)
unnamed: R40.1, U15.1 (Q1)
unnamed: R41.1, U8.6 (3Y)
unnamed: SW9.1, U1.44 (PA11)
unnamed: SW10.1, U1.45 (PA12)
unnamed: J11.1, U8.3 (2A)
unnamed: J11.6, U8.5 (3A)
VBUS: C1.1, C20.1, D10.2 (A), D11.2 (A), J6.1, J9.A4 (VBUS), J9.A9 (VBUS), J9.B4 (VBUS), J9.B9 (VBUS), U4.5 (VBUS), U12.4 (VDD)

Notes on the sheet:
Label: 1:VBUS 2:GND 3:PA7 4:PA5 5:PA1 6:PB0 7:PA6 8:PA4
STM32: -UART1_TX(37) CONNECTED TO ESP -UART1_RX(38) CONNECTED TO ESP -UART2_TX(16) SWITCH RELAY -UART2_RX(17) SWITCH RELAY -UART3_TX(29) SERIAL DEBUG CONNECTOR -UART3_RX(30) SERIAL DEBUG CONNECTOR
Serial Switch Relay
EEPROM: -EEP_SCL(6) -EEP_SDA(5)
I2S Bus STM32:
BB_COLS
ESP32: -ESP_SDA(24) -ESP_SCL(25)
label: 1:RP_22 2:RN_19 3:LP_25 4:LN_23 5:PC6 6:PC7
ESP32 WIFI
Analog Filter Capacitors
I2C BUS SCL
PWR_LED
Keyboard Headers
Crystal Oscilator
BATT CHIP
Label: 1:VCC 2:VCC 3:NRST 4:PA13 5:PA14 6:GND
Wm8960 Header
CH340N: -CH_RXD(7) SWITCH RELAY -CH_TXD(8) SWITCH RELAY
BOOT/RESET CIRCUIT
NOTES: -BOOT_STM goes out to BOOT0 pin on STM -RESET_STM goes out to NRST pin on STM -BOOT_ESP goes out to IO0 on ESP -RESET_ESP goes out to EN on ESP For the following 4 pins above, the existing circuits connected to each of these pins would then be replaced if this circuit is correct. -CH_RTS goe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
USB-C
Boot switch
3.3V to all board
BB_ROWS
Decoupling Capacitors
Main CPU
Reset switch
-I2S2_ext_SD(10) -> BCLK -I2S2_SD(11) -> DACLRC -I2S3_SD(53) -> ADCDAT -I2S3_ext_SD(52) -> ADCLRC -I2S3_CK(51) -> DACDAT
ESP32: -UART1_TX(10) CONNECTED TO STM -UART1_RX(11) CONNECTED TO STM -ESP_RXD0(36) SWITCH RELAY -ESP_TXD0(37) SWITCH RELAY
Notes
Label: 1:VCC 2: IO47 3: IO48 4:GND
Power Usage
WM8960
Serial Debug Connector
I2C BUS SDA
Label: 1:VCC 2:PB12 3:PB13 4:PB14 5:PB15 6:PB2 7:PB3 8:PB4 9:GND
Label: 1: VCC 2: PB10 3: PB11 4: GND
V_OUT
STM32: -PB6(58) STM_SCL -PB7(59) STM_SDA
EEPROM
